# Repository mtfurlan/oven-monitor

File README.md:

# Oven Monitor
d1 mini + oled + k type thermocouple to track oven temperature

## Features
* Displays oven temperature if over 70C
* Reports temperature over mqtt every 60 seconds or on a 5 degree change

## Code features
* rolling average for ADC
* The rest is thermostat code

## BOM
* adafruit AD8495 Breakout: https://www.adafruit.com/product/1778
* K type thermocouple
* d1 mini
* oled display i2c SSD1306 128X64

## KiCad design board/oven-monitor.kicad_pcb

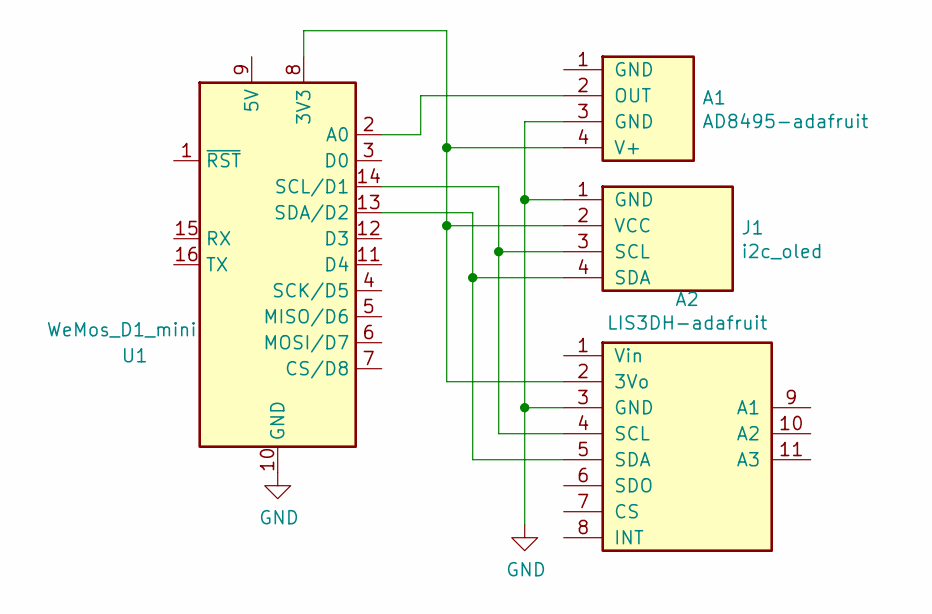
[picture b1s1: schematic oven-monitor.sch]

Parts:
A1: AD8495-adafruit
A2: LIS3DH-adafruit
J1: i2c_oled
U1: WeMos_D1_mini; WEMOS_D1_mini_light

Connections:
GND: A1.3 (GND), A2.3 (GND), J1.1 (GND), U1.10 (GND)
unnamed: A1.2 (OUT), U1.2 (A0)
unnamed: A1.4 (V+), A2.2 (3Vo), J1.2 (VCC), U1.8 (3V3)
unnamed: A2.4 (SCL), J1.3 (SCL), U1.14 (SCL/D1)
unnamed: A2.5 (SDA), J1.4 (SDA), U1.13 (SDA/D2)

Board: 2 copper layers, 4 parts (1 on the bottom side), 5 nets, no tracks yet.

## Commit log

2019-10-14 working commit
2019-10-14 note code feature in readme
2020-02-24 try to refactor to make parameters more clear, and make mqtt optional
2020-02-29 feat: add tap detection to wake screen or change unit
    uinsg LIS3DH
2020-03-02 add pcb with gitignore
